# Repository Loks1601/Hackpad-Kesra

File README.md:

HACKPAD - FOR GAMING AND SIMULATIONS 

This project is a compact RGB macro pad built around the Seeed Studio XIAO RP2040.
It uses diode-isolated push buttons for reliable key detection and SK6812 Mini addressable RGB LEDs for per-key lighting effects.

The design focuses on: (KEY FEATURES)

1.Programmable Multi-Button Input Panel

2.Multi-Layer Operation

3.KMK + CircuitPython Firmware

4.Reliable Input Handling.

5.Optional Rotary Encoder Support

6.Expandable & PCB-Friendly Design

  SCHEMATICS !

  PCB WIREFRAME -   

  3D CASE -

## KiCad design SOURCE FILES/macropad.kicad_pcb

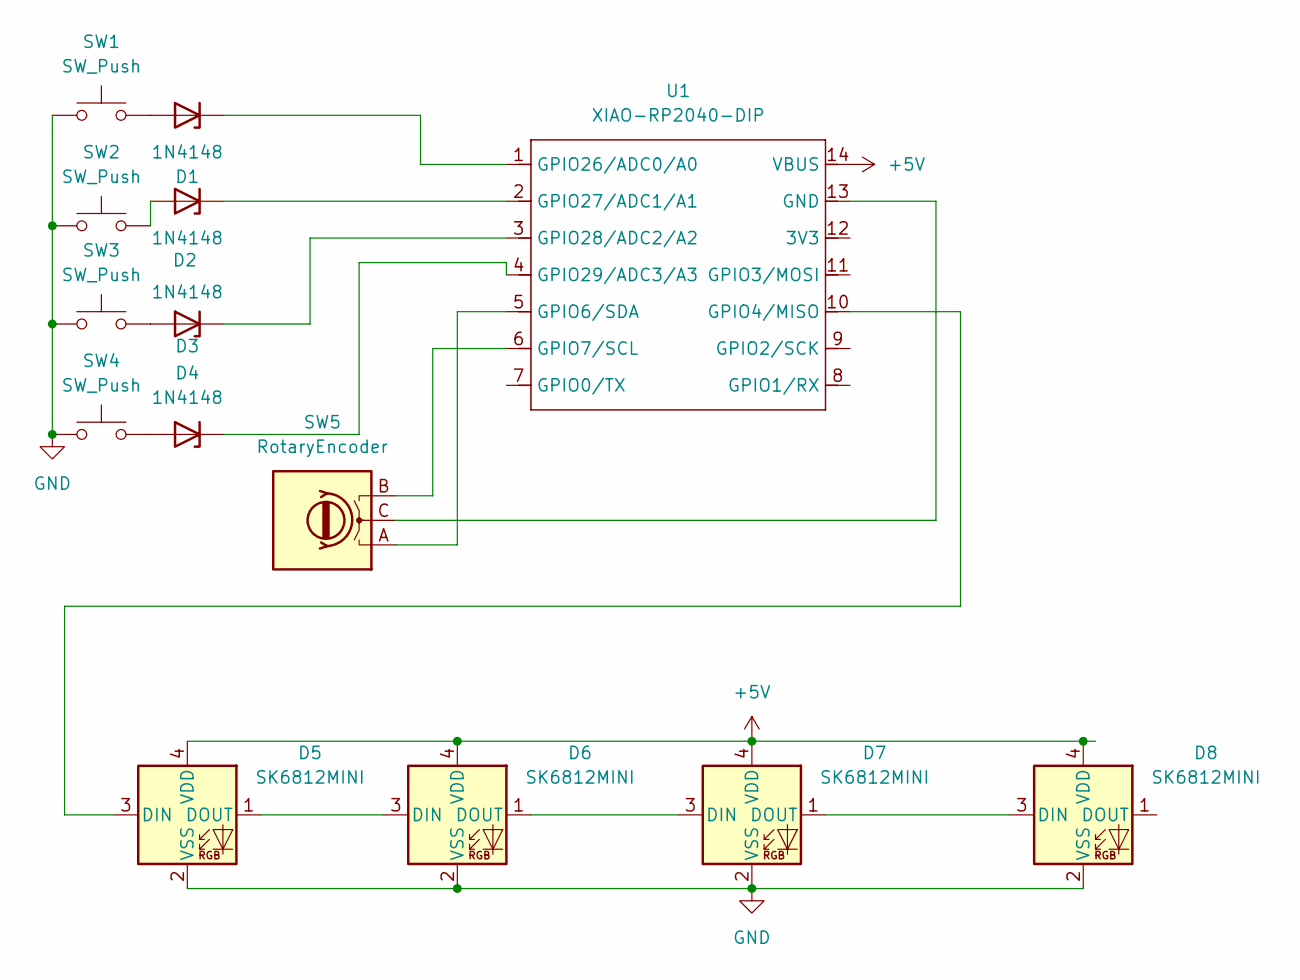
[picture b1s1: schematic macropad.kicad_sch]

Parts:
D1, D2, D3, D4: 1N4148; D_DO-41_SOD81_P10.16mm_Horizontal
D5, D6, D7, D8: SK6812MINI; LED_SK6812MINI_PLCC4_3.5x3.5mm_P1.75mm
SW1, SW2, SW3, SW4: SW_Push; SW_Cherry_MX_1.00u_PCB
SW5: RotaryEncoder; RotaryEncoder_Alps_EC12E_Vertical_H20mm
U1: XIAO-RP2040-DIP

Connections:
+5V: D5.4 (VDD), D6.4 (VDD), D7.4 (VDD), D8.4 (VDD), U1.14 (VBUS)
GND: D5.2 (VSS), D6.2 (VSS), D7.2 (VSS), D8.2 (VSS), SW1.1, SW2.1, SW3.1, SW4.1
unnamed: D1.2 (A), SW1.2
unnamed: D1.1 (K), U1.1 (GPIO26/ADC0/A0)
unnamed: D2.2 (A), SW2.2
unnamed: D2.1 (K), U1.2 (GPIO27/ADC1/A1)
unnamed: D3.2 (A), SW3.2
unnamed: D3.1 (K), U1.3 (GPIO28/ADC2/A2)
unnamed: D4.2 (A), SW4.2
unnamed: D4.1 (K), U1.4 (GPIO29/ADC3/A3)
unnamed: D5.3 (DIN), U1.10 (GPIO4/MISO)
unnamed: D5.1 (DOUT), D6.3 (DIN)
unnamed: D6.1 (DOUT), D7.3 (DIN)
unnamed: D7.1 (DOUT), D8.3 (DIN)
unnamed: SW5.C, U1.13 (GND)
unnamed: SW5.A, U1.5 (GPIO6/SDA)
unnamed: SW5.B, U1.6 (GPIO7/SCL)

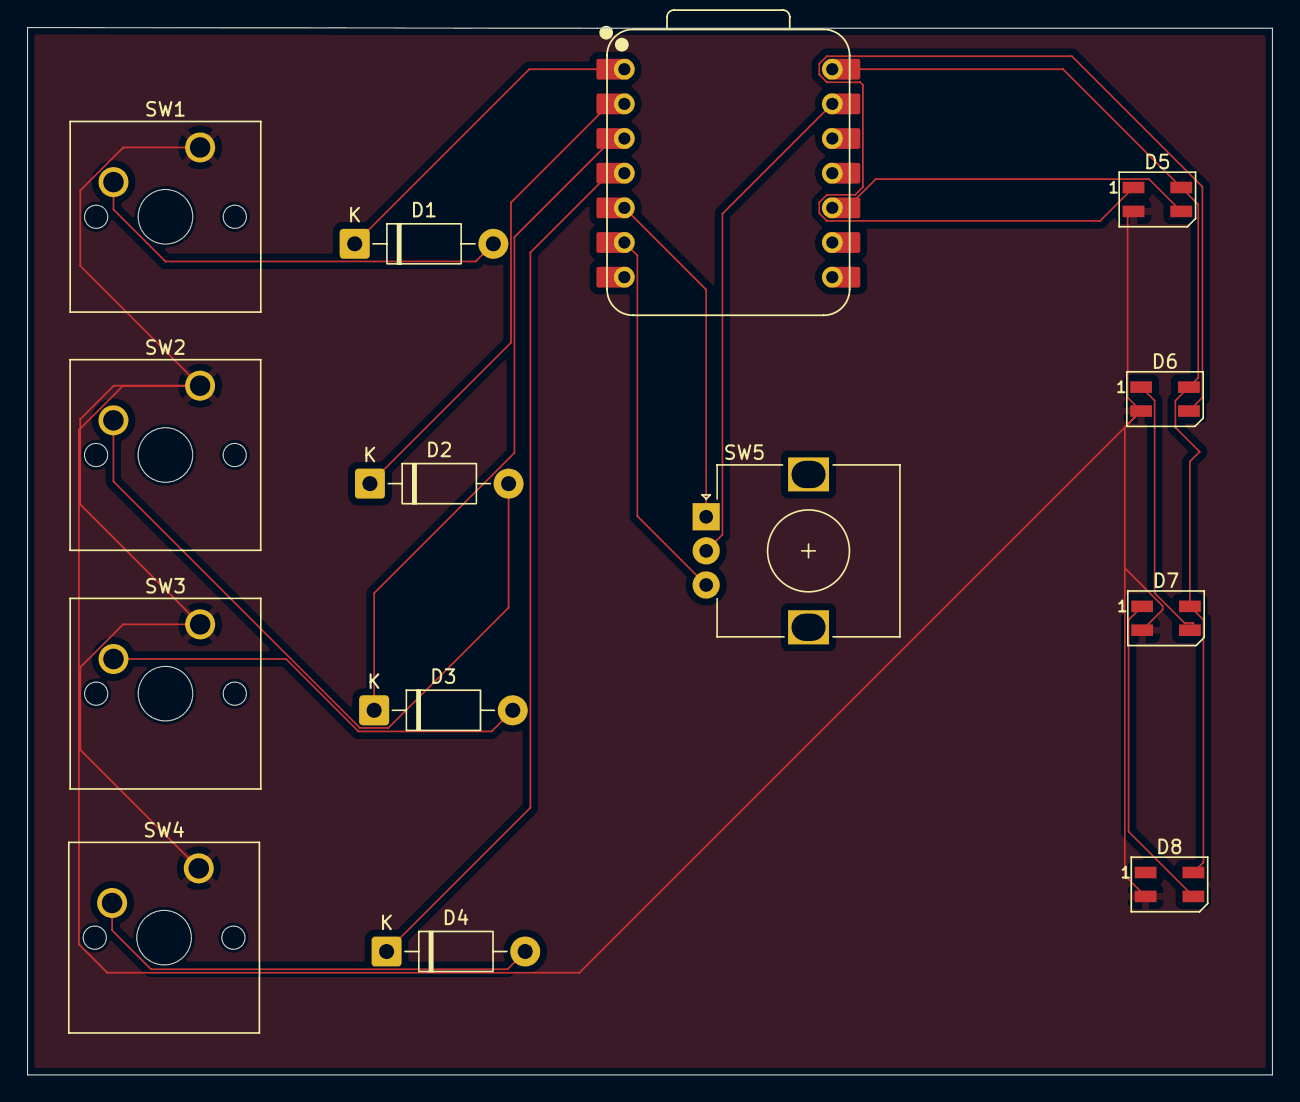
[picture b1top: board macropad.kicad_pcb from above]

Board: 4 copper layers, 91.2 x 76.8 mm, 14 parts (0 on the bottom side), 17 nets.

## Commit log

2025-12-23 Create dxf
2025-12-23 Create hackpad
2025-12-23 Enhance README with key features and images
    Added key features section and visual assets.
2025-12-24 Add files via upload
    ALL PCB FILES
2025-12-24 Add files via upload
    pcb images
2025-12-24 Update README with PCB and 3D case images
    Added images for PCB wireframe and 3D case.
